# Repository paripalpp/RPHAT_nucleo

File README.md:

# RPHAT_nucleo

# connector
|Connector|pin number|nucleo pin|
|---|---|---|
J5|1|PC_0
J5|2|PC_1
J5|3|PC_2
J5|4|PC_3
J5|5|GND
J6|1|PC_4
J6|2|PC_5
J6|3|PC_6
J6|4|PC_7
J6|5|GND
J7|1|PC_8
J7|2|PC_9
J7|3|PC_10
J7|4|PC_11
J7|5|GND
J8|1|PC_12
J8|2|PC_13
J8|3|PC_14
J8|4|PC_15
J8|5|GND
# 注意！！
V0のボードは CAN2 の PB12 と PB13 がつながってますが、CAN TX と CAN RX が逆なので、使用しない又はプリントを切ってつなぎなおすなどをしてください。
 
V1のボードは解決済み。
# LISENCE
<br />This work is licensed under a <a rel="license" href="http://creativecommons.org/licenses/by/4.0/">Creative Commons Attribution 4.0 International License</a>.
<br />この 作品 は <a rel="license" href="http://creativecommons.org/licenses/by/4.0/">クリエイティブ・コモンズ 表示 4.0 国際 ライセンス</a>の下に提供されています。

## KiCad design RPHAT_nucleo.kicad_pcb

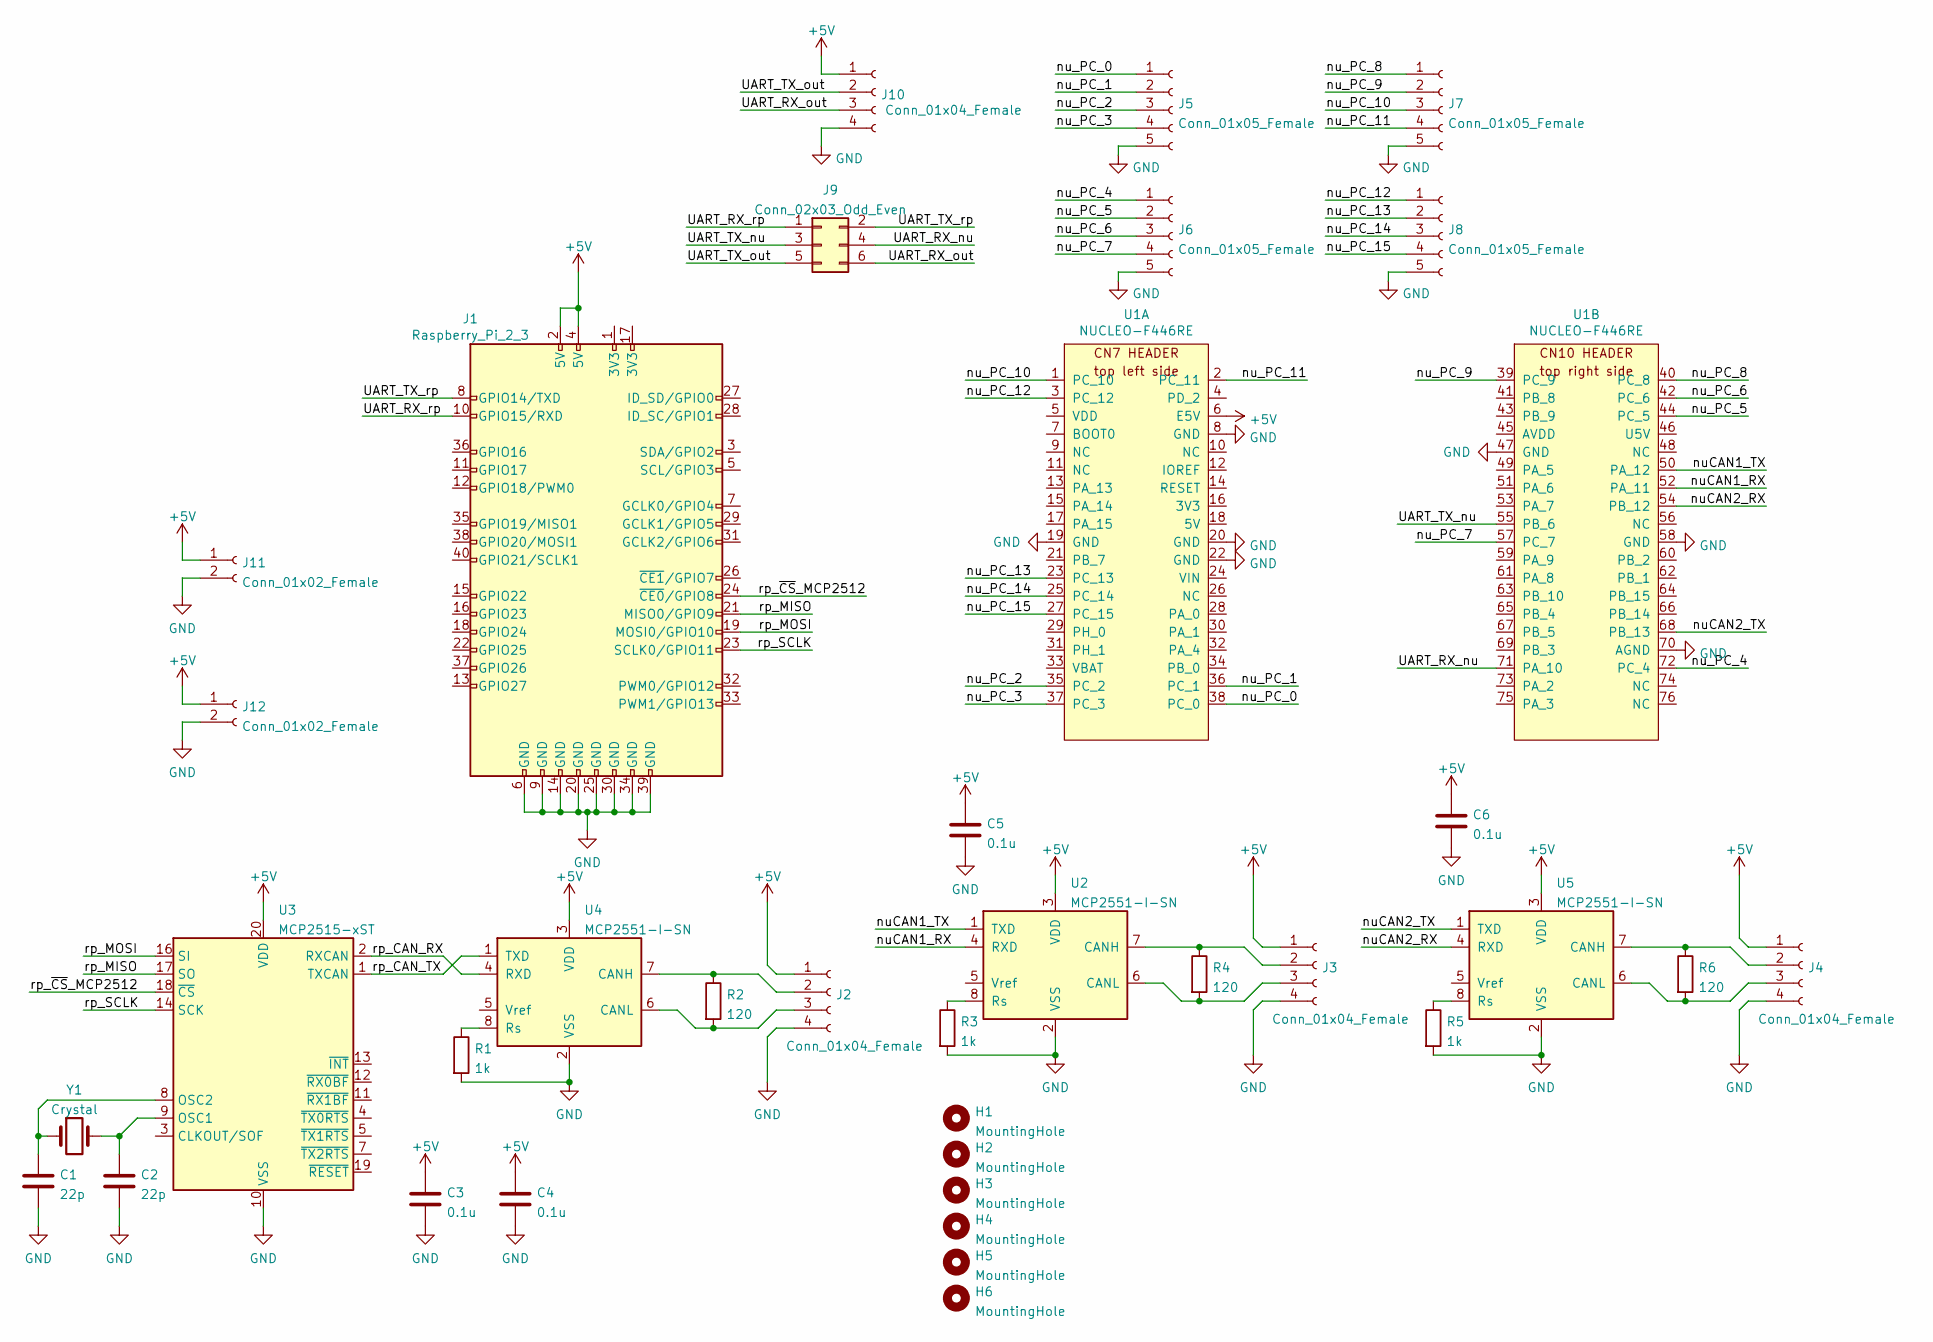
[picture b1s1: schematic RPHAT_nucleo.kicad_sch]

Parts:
C1, C2: 22p; C_0603_1608Metric
C3, C4, C5, C6: 0.1u; C_0603_1608Metric
H1, H2, H3, H4, H5, H6: MountingHole; MountingHole_3.2mm_M3_Pad_Via
J1: Raspberry_Pi_2_3; RaspberryPi_HAT_Connector_4hole
J2, J3, J4, J10: Conn_01x04_Female; JST_XA_S04B-XASK-1_1x04_P2.50mm_Horizontal
J5, J6, J7, J8: Conn_01x05_Female; JST_XA_S05B-XASK-1_1x05_P2.50mm_Horizontal
J9: Conn_02x03_Odd_Even; PinHeader_2x03_P2.54mm_Vertical
J11, J12: Conn_01x02_Female; JST_XA_S02B-XASK-1_1x02_P2.50mm_Horizontal
R1, R3, R5: 1k; R_0603_1608Metric
R2, R4, R6: 120; R_0603_1608Metric
U1: NUCLEO-F446RE; Nucleo-64_ST_morpho
U2, U4, U5: MCP2551-I-SN; SOIC-8_3.9x4.9mm_P1.27mm
U3: MCP2515-xST; TSSOP-20_4.4x6.5mm_P0.65mm
Y1: Crystal; Crystal_SMD_HC49-SD

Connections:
+5V: C3.1, C4.1, C5.1, C6.1, J1.2 (5V), J1.4 (5V), J2.1, J3.1, J4.1, J10.1, J11.1, J12.1, U1.6 (E5V), U2.3 (VDD), U3.20 (VDD), U4.3 (VDD), U5.3 (VDD)
/UART_RX_nu: J9.4, U1.71 (PA_10)
/UART_RX_out: J9.6, J10.3
/UART_RX_rp: J1.10 (GPIO15/RXD), J9.1
/UART_TX_nu: J9.3, U1.55 (PB_6)
/UART_TX_out: J9.5, J10.2
/UART_TX_rp: J1.8 (GPIO14/TXD), J9.2
/nuCAN1_RX: U1.52 (PA_11), U2.4 (RXD)
/nuCAN1_TX: U1.50 (PA_12), U2.1 (TXD)
/nuCAN2_RX: U1.54 (PB_12), U5.4 (RXD)
/nuCAN2_TX: U1.68 (PB_13), U5.1 (TXD)
/nu_PC_0: J5.1, U1.38 (PC_0)
/nu_PC_1: J5.2, U1.36 (PC_1)
/nu_PC_2: J5.3, U1.35 (PC_2)
/nu_PC_3: J5.4, U1.37 (PC_3)
/nu_PC_4: J6.1, U1.72 (PC_4)
/nu_PC_5: J6.2, U1.44 (PC_5)
/nu_PC_6: J6.3, U1.42 (PC_6)
/nu_PC_7: J6.4, U1.57 (PC_7)
/nu_PC_8: J7.1, U1.40 (PC_8)
/nu_PC_9: J7.2, U1.39 (PC_9)
/nu_PC_10: J7.3, U1.1 (PC_10)
/nu_PC_11: J7.4, U1.2 (PC_11)
/nu_PC_12: J8.1, U1.3 (PC_12)
/nu_PC_13: J8.2, U1.23 (PC_13)
/nu_PC_14: J8.3, U1.25 (PC_14)
/nu_PC_15: J8.4, U1.27 (PC_15)
/rp_CAN_RX: U3.2 (RXCAN), U4.4 (RXD)
/rp_CAN_TX: U3.1 (TXCAN), U4.1 (TXD)
/rp_MISO: J1.21 (MISO0/GPIO9), U3.17 (SO)
/rp_MOSI: J1.19 (MOSI0/GPIO10), U3.16 (SI)
/rp_SCLK: J1.23 (SCLK0/GPIO11), U3.14 (SCK)
/rp_~CS_MCP2512: J1.24 (~CE0/GPIO8), U3.18 (~CS)
GND: C1.2, C2.2, C3.2, C4.2, C5.2, C6.2, J1.6 (GND), J1.9 (GND), J1.14 (GND), J1.20 (GND), J1.25 (GND), J1.30 (GND), J1.34 (GND), J1.39 (GND), J2.4, J3.4, J4.4, J5.5, J6.5, J7.5, J8.5, J10.4, J11.2, J12.2, R1.2, R3.2, R5.2, U1.8 (GND), U1.19 (GND), U1.20 (GND), U1.22 (GND), U1.47 (GND), U1.58 (GND), U1.70 (AGND), U2.2 (VSS), U3.10 (VSS), U4.2 (VSS), U5.2 (VSS)
unnamed: C1.1, U3.8 (OSC2), Y1.1
unnamed: C2.1, U3.9 (OSC1), Y1.2
unnamed: J2.2, R2.1, U4.7 (CANH)
unnamed: J2.3, R2.2, U4.6 (CANL)
unnamed: J3.2, R4.1, U2.7 (CANH)
unnamed: J3.3, R4.2, U2.6 (CANL)
unnamed: J4.2, R6.1, U5.7 (CANH)
unnamed: J4.3, R6.2, U5.6 (CANL)
unnamed: R1.1, U4.8 (Rs)
unnamed: R3.1, U2.8 (Rs)
unnamed: R5.1, U5.8 (Rs)

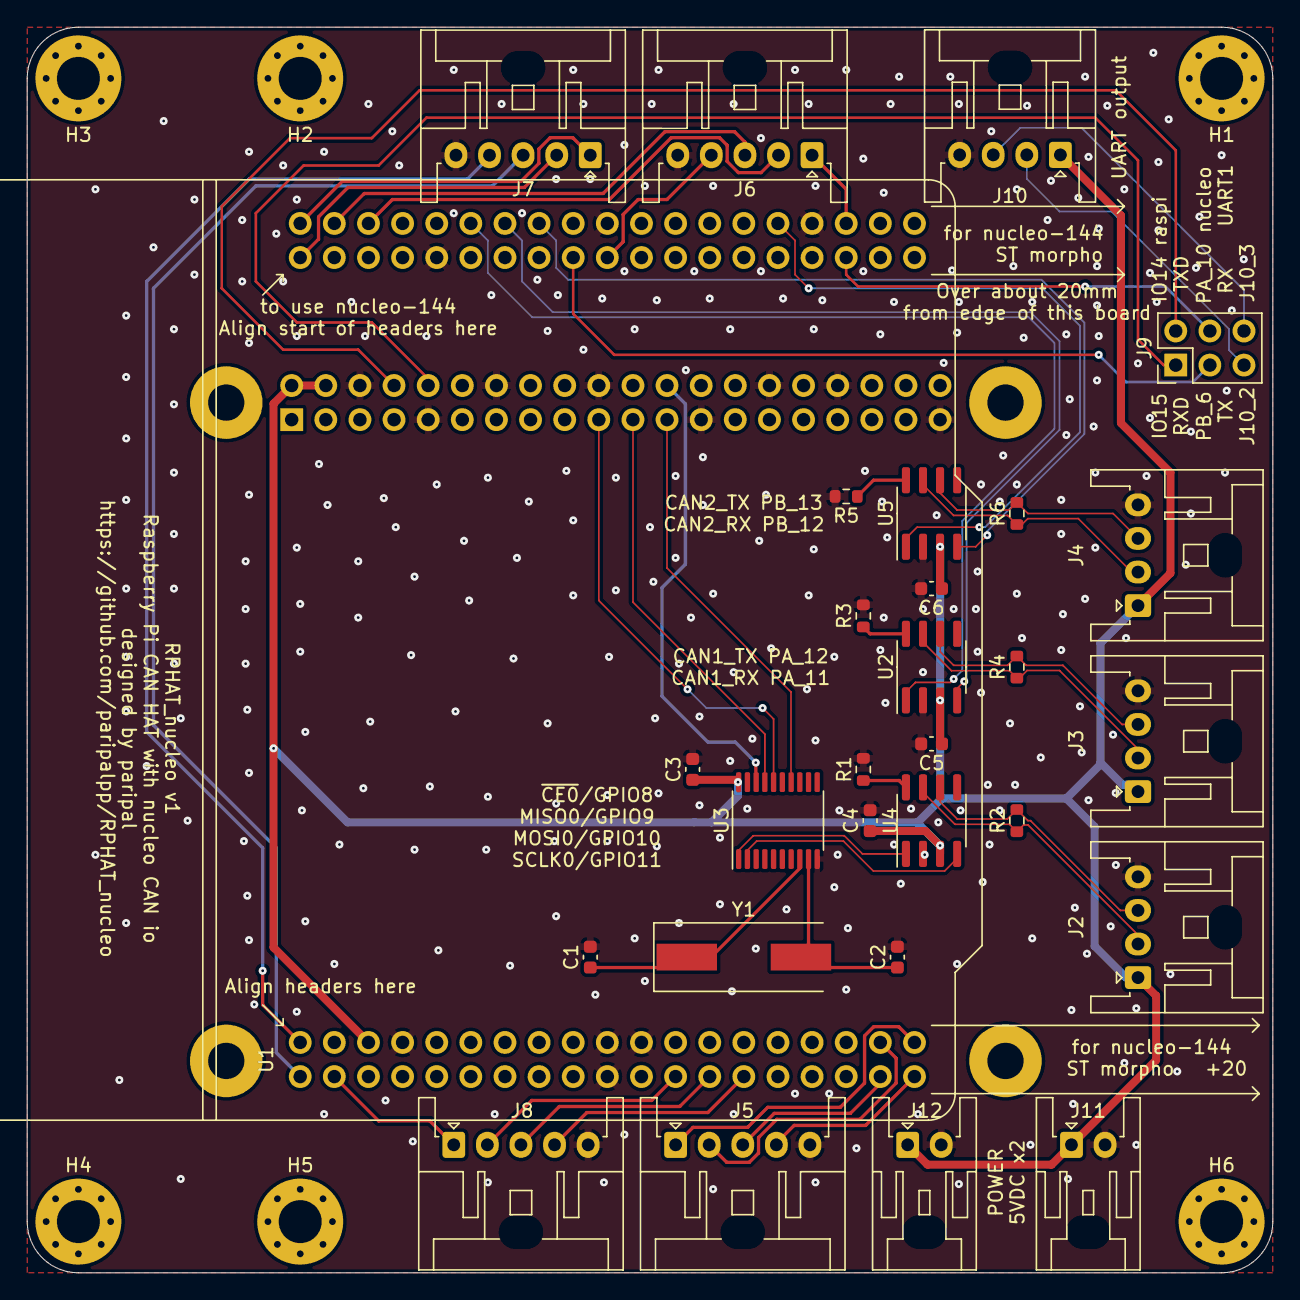
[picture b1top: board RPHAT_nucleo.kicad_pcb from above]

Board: 2 copper layers, 92.7 x 92.7 mm, 36 parts (0 on the bottom side), 45 nets.

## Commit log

2021-12-27 to 6.0
2022-03-13 some
2022-03-18 edit some net class
2022-03-21 complete
2022-03-21 views added
2022-04-20 Update README.md
    CAN2 の間違った配線の注意書きを追加
2022-05-27 v1 comp
